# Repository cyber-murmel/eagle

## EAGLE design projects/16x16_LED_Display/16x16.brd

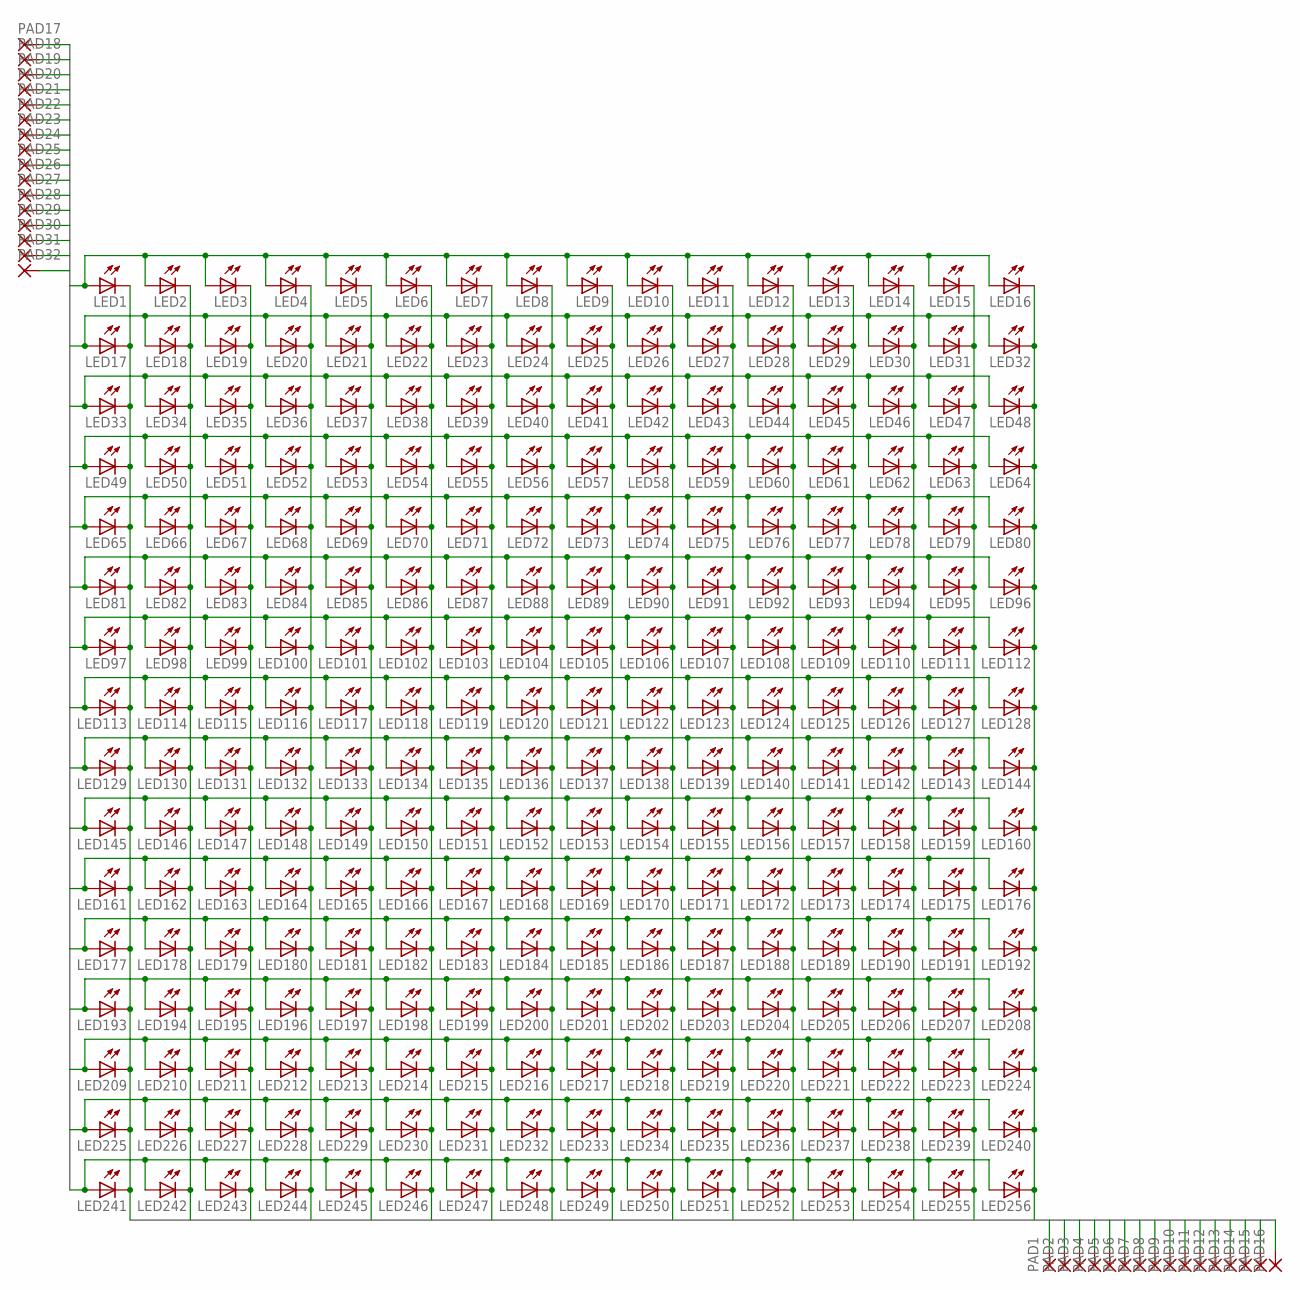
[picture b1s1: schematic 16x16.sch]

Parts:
LED1, LED2, LED3, LED4, LED5, LED6, LED7, LED8, LED9, LED10, LED11, LED12, LED13, LED14, LED15, LED16, LED17, LED18, LED19, LED20, LED21, LED22, LED23, LED24, LED25, LED26, LED27, LED28, LED29, LED30, LED31, LED32, LED33, LED34, LED35, LED36, LED37, LED38, LED39, LED40, LED41, LED42, LED43, LED44, LED45, LED46, LED47, LED48, LED49, LED50, LED51, LED52, LED53, LED54, LED55, LED56, LED57, LED58, LED59, LED60, LED61, LED62, LED63, LED64, LED65, LED66, LED67, LED68, LED69, LED70, LED71, LED72, LED73, LED74, LED75, LED76, LED77, LED78, LED79, LED80, LED81, LED82, LED83, LED84, LED85, LED86, LED87, LED88, LED89, LED90, LED91, LED92, LED93, LED94, LED95, LED96, LED97, LED98, LED99, LED100, LED101, LED102, LED103, LED104, LED105, LED106, LED107, LED108, LED109, LED110, LED111, LED112, LED113, LED114, LED115, LED116, LED117, LED118, LED119, LED120, LED121, LED122, LED123, LED124, LED125, LED126, LED127, LED128, LED129, LED130, LED131, LED132, LED133, LED134, LED135, LED136, LED137, LED138, LED139, LED140, LED141, LED142, LED143, LED144, LED145, LED146, LED147, LED148, LED149, LED150, LED151, LED152, LED153, LED154, LED155, LED156, LED157, LED158, LED159, LED160, LED161, LED162, LED163, LED164, LED165, LED166, LED167, LED168, LED169, LED170, LED171, LED172, LED173, LED174, LED175, LED176, LED177, LED178, LED179, LED180, LED181, LED182, LED183, LED184, LED185, LED186, LED187, LED188, LED189, LED190, LED191, LED192, LED193, LED194, LED195, LED196, LED197, LED198, LED199, LED200, LED201, LED202, LED203, LED204, LED205, LED206, LED207, LED208, LED209, LED210, LED211, LED212, LED213, LED214, LED215, LED216, LED217, LED218, LED219, LED220, LED221, LED222, LED223, LED224, LED225, LED226, LED227, LED228, LED229, LED230, LED231, LED232, LED233, LED234, LED235, LED236, LED237, LED238, LED239, LED240, LED241, LED242, LED243, LED244, LED245, LED246, LED247, LED248, LED249, LED250, LED251, LED252, LED253, LED254, LED255, LED256: LEDSML0603; SML0603
PAD1, PAD2, PAD3, PAD4, PAD5, PAD6, PAD7, PAD8, PAD9, PAD10, PAD11, PAD12, PAD13, PAD14, PAD15, PAD16, PAD17, PAD18, PAD19, PAD20, PAD21, PAD22, PAD23, PAD24, PAD25, PAD26, PAD27, PAD28, PAD29, PAD30, PAD31, PAD32: SMD2; SMD1,27-2,54

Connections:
X0: LED1.C, LED17.C, LED33.C, LED49.C, LED65.C, LED81.C, LED97.C, LED113.C, LED129.C, LED145.C, LED161.C, LED177.C, LED193.C, LED209.C, LED225.C, LED241.C, PAD1.1
X1: LED2.C, LED18.C, LED34.C, LED50.C, LED66.C, LED82.C, LED98.C, LED114.C, LED130.C, LED146.C, LED162.C, LED178.C, LED194.C, LED210.C, LED226.C, LED242.C, PAD2.1
X2: LED3.C, LED19.C, LED35.C, LED51.C, LED67.C, LED83.C, LED99.C, LED115.C, LED131.C, LED147.C, LED163.C, LED179.C, LED195.C, LED211.C, LED227.C, LED243.C, PAD3.1
X3: LED4.C, LED20.C, LED36.C, LED52.C, LED68.C, LED84.C, LED100.C, LED116.C, LED132.C, LED148.C, LED164.C, LED180.C, LED196.C, LED212.C, LED228.C, LED244.C, PAD4.1
X4: LED5.C, LED21.C, LED37.C, LED53.C, LED69.C, LED85.C, LED101.C, LED117.C, LED133.C, LED149.C, LED165.C, LED181.C, LED197.C, LED213.C, LED229.C, LED245.C, PAD5.1
X5: LED6.C, LED22.C, LED38.C, LED54.C, LED70.C, LED86.C, LED102.C, LED118.C, LED134.C, LED150.C, LED166.C, LED182.C, LED198.C, LED214.C, LED230.C, LED246.C, PAD6.1
X6: LED7.C, LED23.C, LED39.C, LED55.C, LED71.C, LED87.C, LED103.C, LED119.C, LED135.C, LED151.C, LED167.C, LED183.C, LED199.C, LED215.C, LED231.C, LED247.C, PAD7.1
X7: LED8.C, LED24.C, LED40.C, LED56.C, LED72.C, LED88.C, LED104.C, LED120.C, LED136.C, LED152.C, LED168.C, LED184.C, LED200.C, LED216.C, LED232.C, LED248.C, PAD8.1
X8: LED9.C, LED25.C, LED41.C, LED57.C, LED73.C, LED89.C, LED105.C, LED121.C, LED137.C, LED153.C, LED169.C, LED185.C, LED201.C, LED217.C, LED233.C, LED249.C, PAD9.1
X9: LED10.C, LED26.C, LED42.C, LED58.C, LED74.C, LED90.C, LED106.C, LED122.C, LED138.C, LED154.C, LED170.C, LED186.C, LED202.C, LED218.C, LED234.C, LED250.C, PAD10.1
X10: LED11.C, LED27.C, LED43.C, LED59.C, LED75.C, LED91.C, LED107.C, LED123.C, LED139.C, LED155.C, LED171.C, LED187.C, LED203.C, LED219.C, LED235.C, LED251.C, PAD11.1
X11: LED12.C, LED28.C, LED44.C, LED60.C, LED76.C, LED92.C, LED108.C, LED124.C, LED140.C, LED156.C, LED172.C, LED188.C, LED204.C, LED220.C, LED236.C, LED252.C, PAD12.1
X12: LED13.C, LED29.C, LED45.C, LED61.C, LED77.C, LED93.C, LED109.C, LED125.C, LED141.C, LED157.C, LED173.C, LED189.C, LED205.C, LED221.C, LED237.C, LED253.C, PAD13.1
X13: LED14.C, LED30.C, LED46.C, LED62.C, LED78.C, LED94.C, LED110.C, LED126.C, LED142.C, LED158.C, LED174.C, LED190.C, LED206.C, LED222.C, LED238.C, LED254.C, PAD14.1
X14: LED15.C, LED31.C, LED47.C, LED63.C, LED79.C, LED95.C, LED111.C, LED127.C, LED143.C, LED159.C, LED175.C, LED191.C, LED207.C, LED223.C, LED239.C, LED255.C, PAD15.1
X15: LED16.C, LED32.C, LED48.C, LED64.C, LED80.C, LED96.C, LED112.C, LED128.C, LED144.C, LED160.C, LED176.C, LED192.C, LED208.C, LED224.C, LED240.C, LED256.C, PAD16.1
Y0: LED1.A, LED2.A, LED3.A, LED4.A, LED5.A, LED6.A, LED7.A, LED8.A, LED9.A, LED10.A, LED11.A, LED12.A, LED13.A, LED14.A, LED15.A, LED16.A, PAD17.1
Y1: LED17.A, LED18.A, LED19.A, LED20.A, LED21.A, LED22.A, LED23.A, LED24.A, LED25.A, LED26.A, LED27.A, LED28.A, LED29.A, LED30.A, LED31.A, LED32.A, PAD18.1
Y2: LED33.A, LED34.A, LED35.A, LED36.A, LED37.A, LED38.A, LED39.A, LED40.A, LED41.A, LED42.A, LED43.A, LED44.A, LED45.A, LED46.A, LED47.A, LED48.A, PAD19.1
Y3: LED49.A, LED50.A, LED51.A, LED52.A, LED53.A, LED54.A, LED55.A, LED56.A, LED57.A, LED58.A, LED59.A, LED60.A, LED61.A, LED62.A, LED63.A, LED64.A, PAD20.1
Y4: LED65.A, LED66.A, LED67.A, LED68.A, LED69.A, LED70.A, LED71.A, LED72.A, LED73.A, LED74.A, LED75.A, LED76.A, LED77.A, LED78.A, LED79.A, LED80.A, PAD21.1
Y5: LED81.A, LED82.A, LED83.A, LED84.A, LED85.A, LED86.A, LED87.A, LED88.A, LED89.A, LED90.A, LED91.A, LED92.A, LED93.A, LED94.A, LED95.A, LED96.A, PAD22.1
Y6: LED97.A, LED98.A, LED99.A, LED100.A, LED101.A, LED102.A, LED103.A, LED104.A, LED105.A, LED106.A, LED107.A, LED108.A, LED109.A, LED110.A, LED111.A, LED112.A, PAD23.1
Y7: LED113.A, LED114.A, LED115.A, LED116.A, LED117.A, LED118.A, LED119.A, LED120.A, LED121.A, LED122.A, LED123.A, LED124.A, LED125.A, LED126.A, LED127.A, LED128.A, PAD24.1
Y8: LED129.A, LED130.A, LED131.A, LED132.A, LED133.A, LED134.A, LED135.A, LED136.A, LED137.A, LED138.A, LED139.A, LED140.A, LED141.A, LED142.A, LED143.A, LED144.A, PAD25.1
Y9: LED145.A, LED146.A, LED147.A, LED148.A, LED149.A, LED150.A, LED151.A, LED152.A, LED153.A, LED154.A, LED155.A, LED156.A, LED157.A, LED158.A, LED159.A, LED160.A, PAD26.1
Y10: LED161.A, LED162.A, LED163.A, LED164.A, LED165.A, LED166.A, LED167.A, LED168.A, LED169.A, LED170.A, LED171.A, LED172.A, LED173.A, LED174.A, LED175.A, LED176.A, PAD27.1
Y11: LED177.A, LED178.A, LED179.A, LED180.A, LED181.A, LED182.A, LED183.A, LED184.A, LED185.A, LED186.A, LED187.A, LED188.A, LED189.A, LED190.A, LED191.A, LED192.A, PAD28.1
Y12: LED193.A, LED194.A, LED195.A, LED196.A, LED197.A, LED198.A, LED199.A, LED200.A, LED201.A, LED202.A, LED203.A, LED204.A, LED205.A, LED206.A, LED207.A, LED208.A, PAD29.1
Y13: LED209.A, LED210.A, LED211.A, LED212.A, LED213.A, LED214.A, LED215.A, LED216.A, LED217.A, LED218.A, LED219.A, LED220.A, LED221.A, LED222.A, LED223.A, LED224.A, PAD30.1
Y14: LED225.A, LED226.A, LED227.A, LED228.A, LED229.A, LED230.A, LED231.A, LED232.A, LED233.A, LED234.A, LED235.A, LED236.A, LED237.A, LED238.A, LED239.A, LED240.A, PAD31.1
Y15: LED241.A, LED242.A, LED243.A, LED244.A, LED245.A, LED246.A, LED247.A, LED248.A, LED249.A, LED250.A, LED251.A, LED252.A, LED253.A, LED254.A, LED255.A, LED256.A, PAD32.1

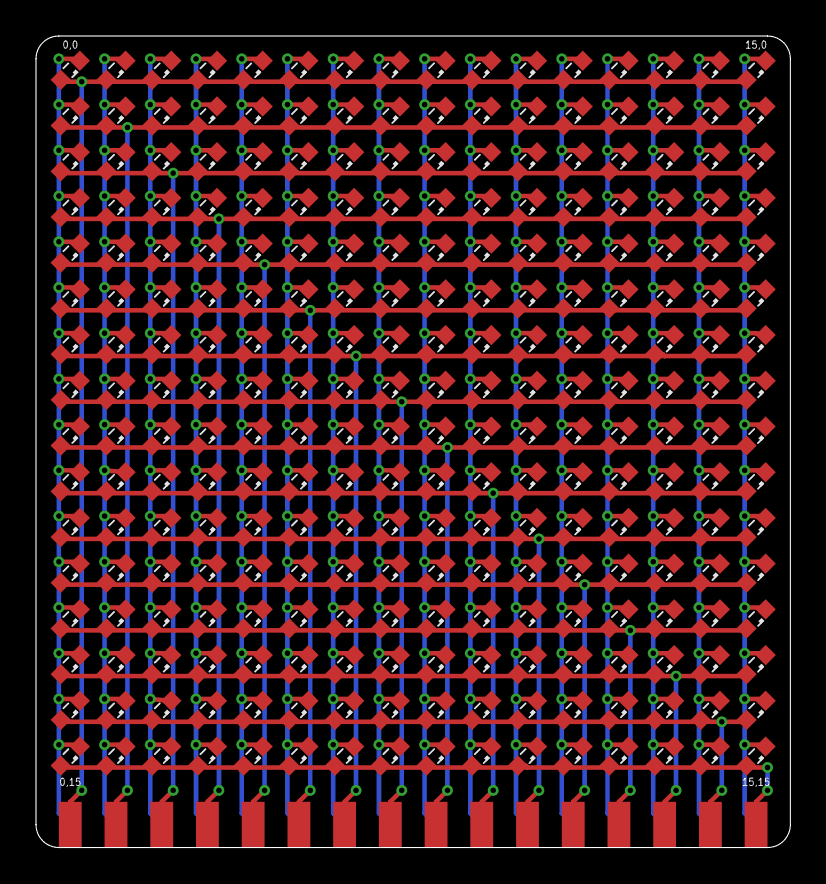
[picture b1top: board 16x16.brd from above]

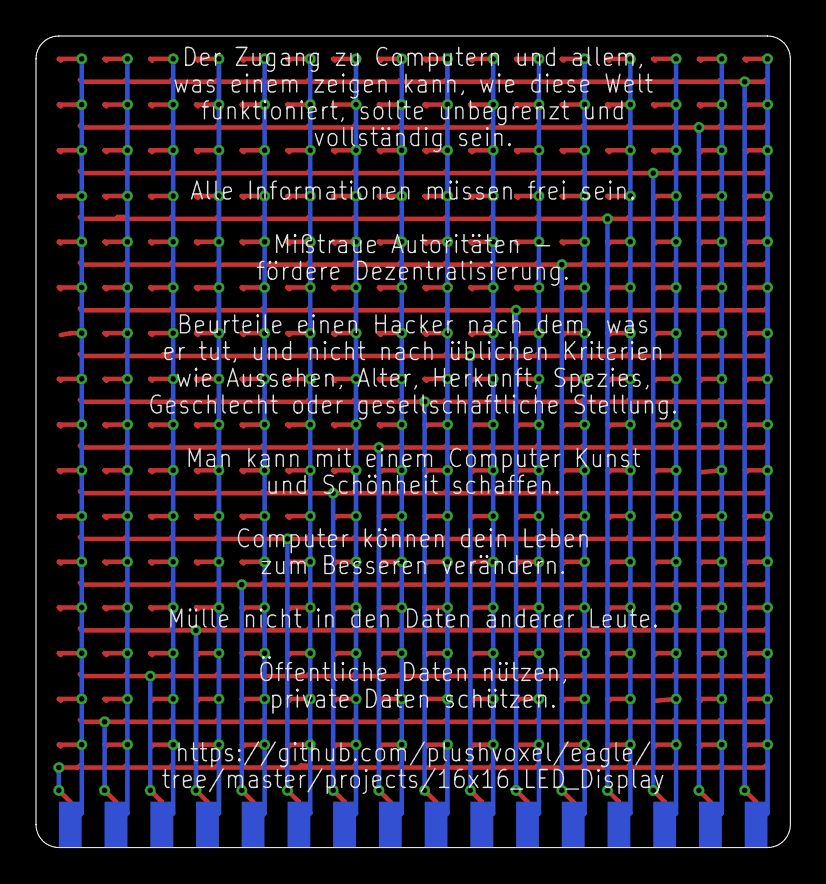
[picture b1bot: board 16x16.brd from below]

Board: 2 copper layers, 41.9 x 45.1 mm, 288 parts (16 on the bottom side), 32 nets.

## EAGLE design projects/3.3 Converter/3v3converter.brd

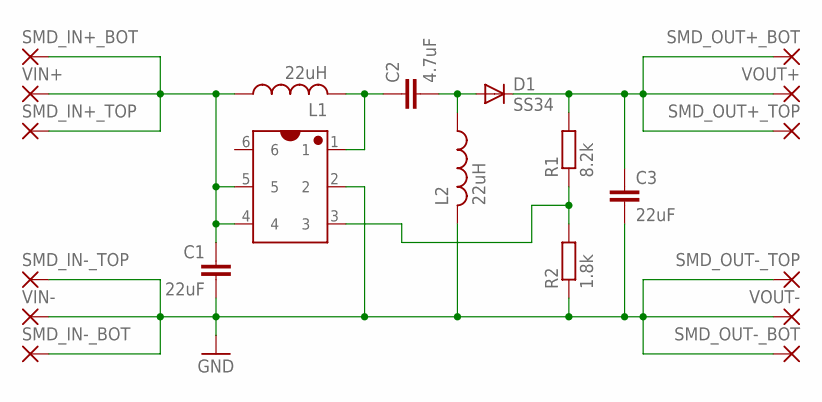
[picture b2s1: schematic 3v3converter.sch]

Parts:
C1, C3: 22uF; C0805
C2: 4.7uF; C0603
D1: SS34; DO214BA
L1, L2: 22uH; FPS
MT3608: mt3608; SOT-23-6
R1: 8.2k; R0603
R2: 1.8k; R0603
SMD_IN+_BOT: SMD5; SMD2,54-5,08
SMD_IN+_TOP: SMD5; SMD2,54-5,08
SMD_IN-_BOT: SMD5; SMD2,54-5,08
SMD_IN-_TOP: SMD5; SMD2,54-5,08
SMD_OUT+_BOT: SMD5; SMD2,54-5,08
SMD_OUT+_TOP: SMD5; SMD2,54-5,08
SMD_OUT-_BOT: SMD5; SMD2,54-5,08
SMD_OUT-_TOP: SMD5; SMD2,54-5,08
VIN+: 1,6/0,9
VIN-: 1,6/0,9
VOUT+: 1,6/0,9
VOUT-: 1,6/0,9

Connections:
GND: C1.2, C3.2, L2.P$2 (2), MT3608.2, R2.1, SMD_IN-_BOT.1, SMD_IN-_TOP.1, SMD_OUT-_BOT.1, SMD_OUT-_TOP.1, VIN-.1, VOUT-.1
unnamed: C1.1, L1.P$1 (1), MT3608.4, MT3608.5, SMD_IN+_BOT.1, SMD_IN+_TOP.1, VIN+.1
unnamed: C2.1, L1.P$2 (2), MT3608.1
unnamed: C2.2, D1.A, L2.P$1 (1)
unnamed: C3.1, D1.C, R1.2, SMD_OUT+_BOT.1, SMD_OUT+_TOP.1, VOUT+.1
unnamed: MT3608.3, R1.1, R2.2

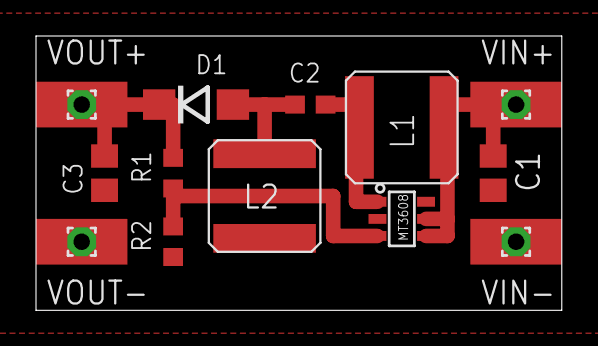
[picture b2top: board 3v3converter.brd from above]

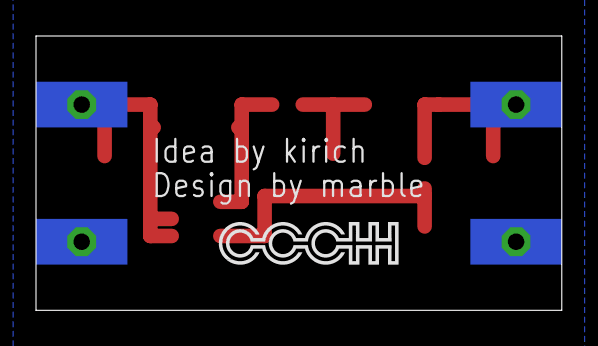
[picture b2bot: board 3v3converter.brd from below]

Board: 2 copper layers, 29.2 x 15.2 mm, 21 parts (4 on the bottom side), 6 nets.

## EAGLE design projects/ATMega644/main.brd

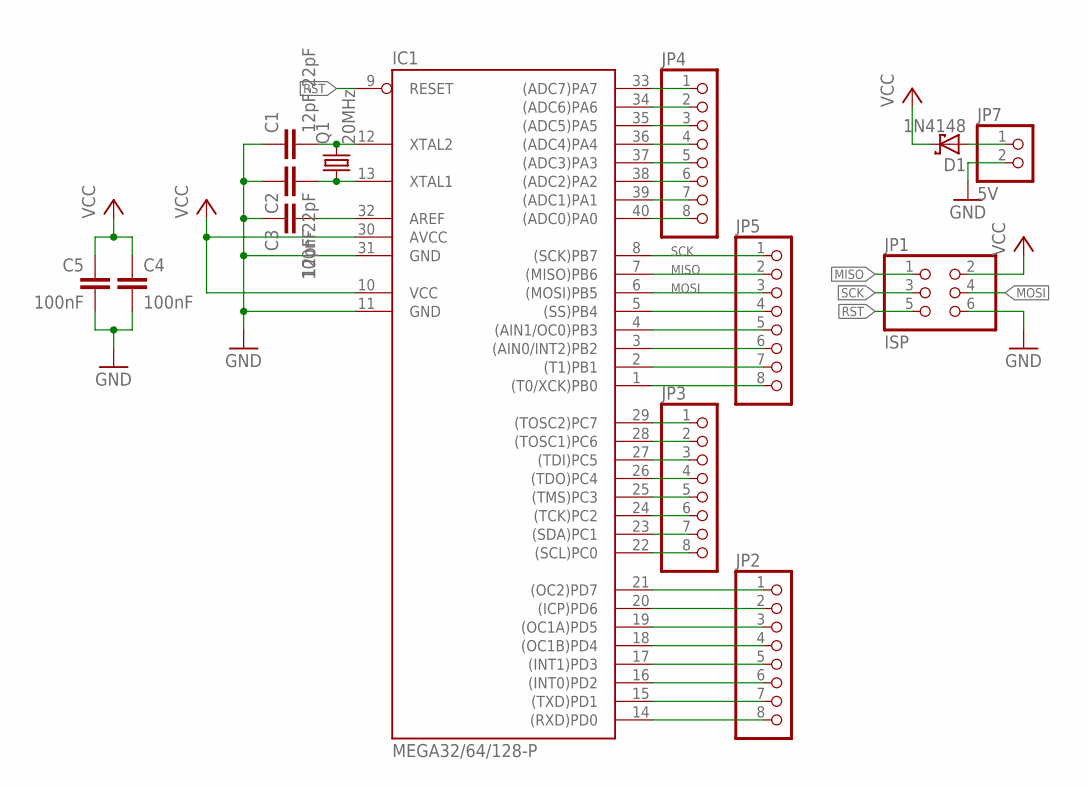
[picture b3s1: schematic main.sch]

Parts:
C1, C2: 12pF-22pF; C0805K
C3, C4, C5: 100nF; C0805K
D1: 1N4148; DO41-7.6
IC1: MEGA32/64/128-P; DIL40
JP1: ISP; 2X03
JP2, JP3, JP4, JP5: PINHD-1X8; 1X08
JP7: 5V; 1X02
Q1: 20MHz; CSM-7X-DU

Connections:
GND: C1.1, C2.1, C3.1, C4.2, C5.2, IC1.11 (GND), IC1.31 (GND), JP1.6, JP7.2
MISO: IC1.7 ((MISO)PB6), JP1.1, JP5.2
MOSI: IC1.6 ((MOSI)PB5), JP1.4, JP5.3
unnamed: C2.2, IC1.13 (XTAL1), Q1.1
unnamed: C1.2, IC1.12 (XTAL2), Q1.2
unnamed: D1.A, JP7.1
unnamed: C3.2, IC1.32 (AREF)
unnamed: IC1.5 ((SS)PB4), JP5.4
unnamed: IC1.4 ((AIN1/OC0)PB3), JP5.5
unnamed: IC1.21 ((OC2)PD7), JP2.1
unnamed: IC1.20 ((ICP)PD6), JP2.2
unnamed: IC1.19 ((OC1A)PD5), JP2.3
unnamed: IC1.18 ((OC1B)PD4), JP2.4
unnamed: IC1.17 ((INT1)PD3), JP2.5
unnamed: IC1.16 ((INT0)PD2), JP2.6
unnamed: IC1.15 ((TXD)PD1), JP2.7
unnamed: IC1.14 ((RXD)PD0), JP2.8
unnamed: IC1.29 ((TOSC2)PC7), JP3.1
unnamed: IC1.28 ((TOSC1)PC6), JP3.2
unnamed: IC1.27 ((TDI)PC5), JP3.3
unnamed: IC1.26 ((TDO)PC4), JP3.4
unnamed: IC1.25 ((TMS)PC3), JP3.5
unnamed: IC1.24 ((TCK)PC2), JP3.6
unnamed: IC1.23 ((SDA)PC1), JP3.7
unnamed: IC1.22 ((SCL)PC0), JP3.8
unnamed: IC1.33 ((ADC7)PA7), JP4.1
unnamed: IC1.34 ((ADC6)PA6), JP4.2
unnamed: IC1.35 ((ADC5)PA5), JP4.3
unnamed: IC1.36 ((ADC4)PA4), JP4.4
unnamed: IC1.37 ((ADC3)PA3), JP4.5
unnamed: IC1.38 ((ADC2)PA2), JP4.6
unnamed: IC1.39 ((ADC1)PA1), JP4.7
unnamed: IC1.40 ((ADC0)PA0), JP4.8
unnamed: IC1.3 ((AIN0/INT2)PB2), JP5.6
unnamed: IC1.2 ((T1)PB1), JP5.7
unnamed: IC1.1 ((T0/XCK)PB0), JP5.8
RST: IC1.9 (RESET), JP1.5
SCK: IC1.8 ((SCK)PB7), JP1.3, JP5.1
VCC: C4.1, C5.1, D1.C, IC1.10 (VCC), IC1.30 (AVCC), JP1.2

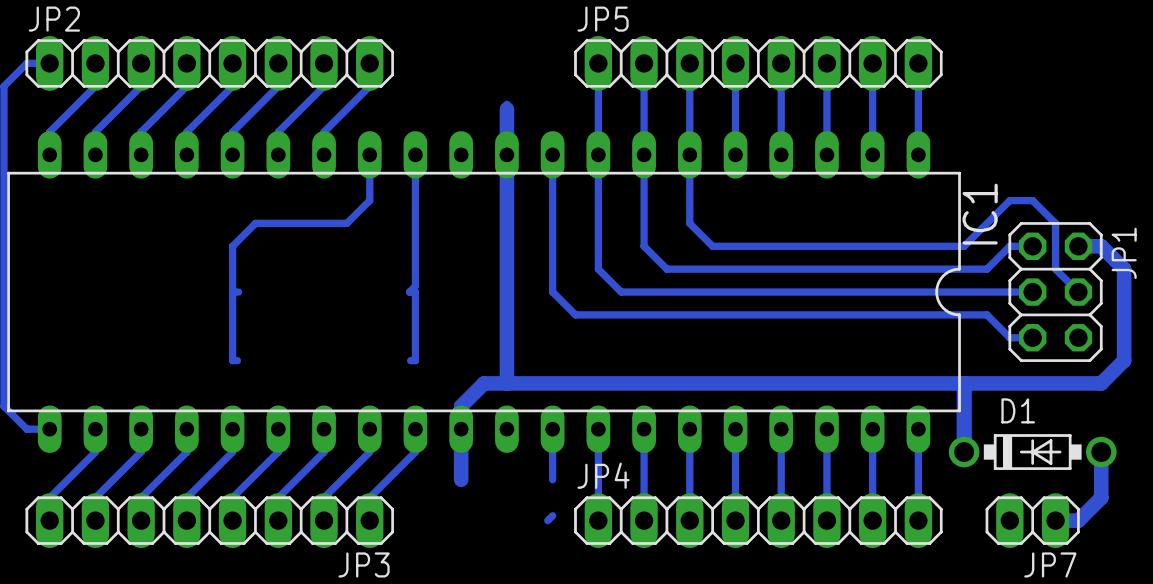
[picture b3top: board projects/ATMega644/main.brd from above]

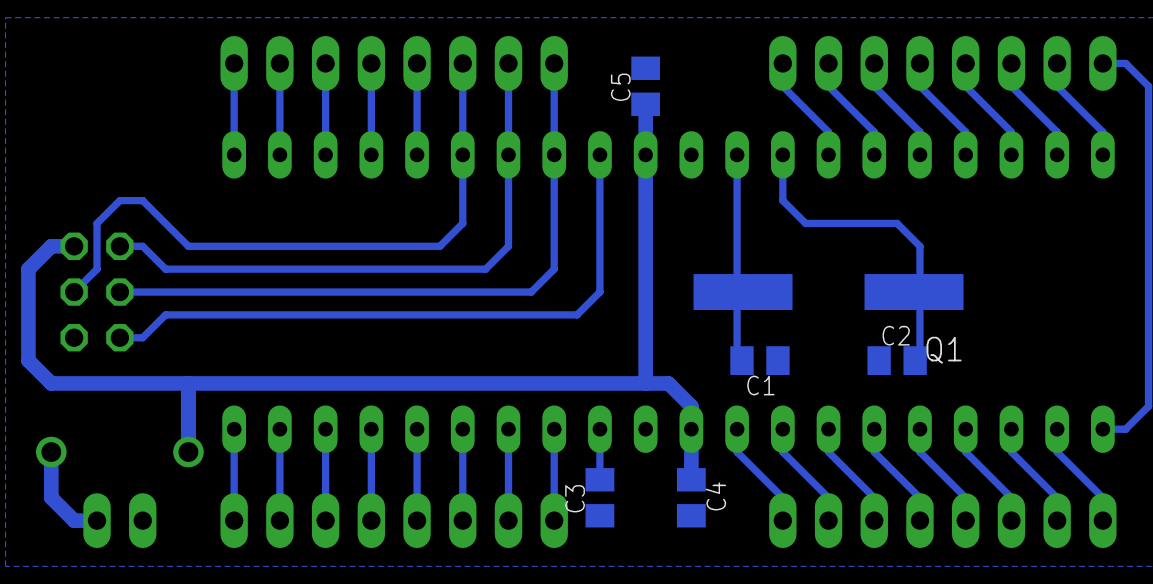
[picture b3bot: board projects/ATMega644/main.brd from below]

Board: 2 copper layers, 14 parts (6 on the bottom side), 39 nets.

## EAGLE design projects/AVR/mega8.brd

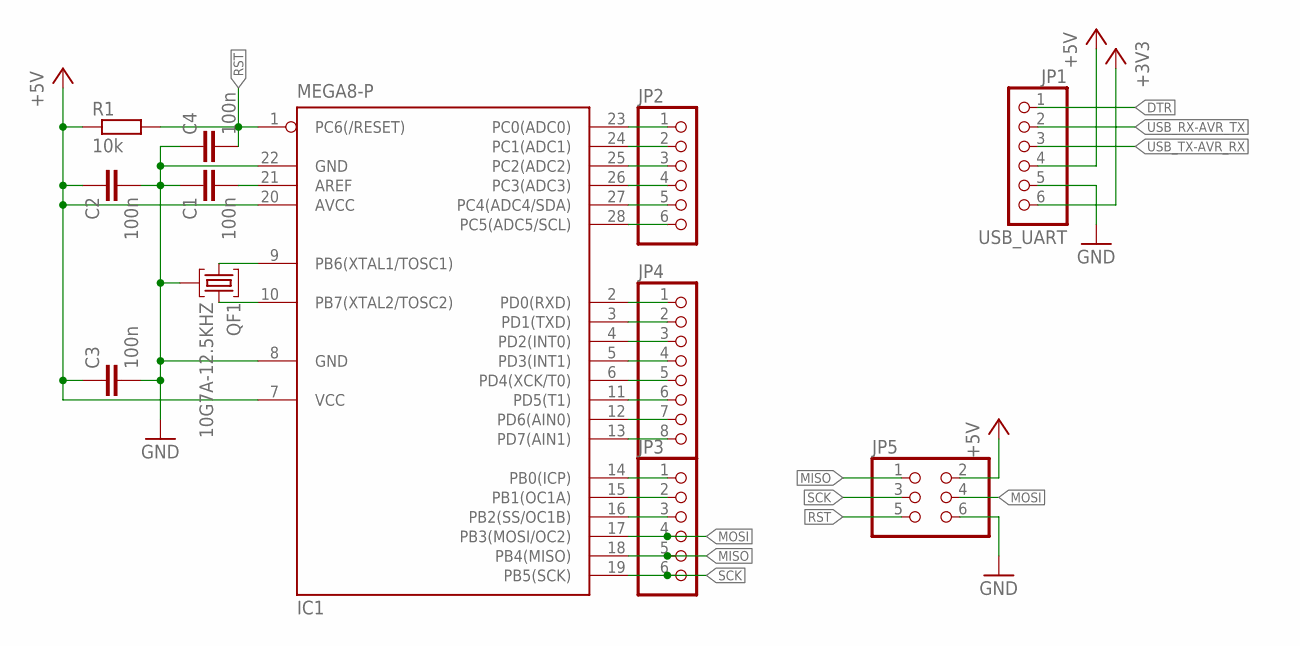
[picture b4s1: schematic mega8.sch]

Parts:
C1, C2, C3, C4: 100n; C0603
IC1: MEGA8-P; DIL28-3
JP1: USB_UART; 1X06
JP2, JP3: PINHD-1X6; 1X06
JP4: PINHD-1X8; 1X08
JP5: PINHD-2X3; 2X03
QF1: 10G7A-12.5KHZ; HC49U
R1: 10k; R0603

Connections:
+3V3: JP1.6
+5V: C2.1, C3.1, IC1.7 (VCC), IC1.20 (AVCC), JP1.4, JP5.2, R1.1
DTR: JP1.1
GND: C1.1, C2.2, C3.2, C4.1, IC1.8 (GND), IC1.22 (GND), JP1.5, JP5.6, QF1.2
MISO: IC1.18 (PB4(MISO)), JP3.5, JP5.1
MOSI: IC1.17 (PB3(MOSI/OC2)), JP3.4, JP5.4
unnamed: IC1.9 (PB6(XTAL1/TOSC1)), QF1.1
unnamed: IC1.10 (PB7(XTAL2/TOSC2)), QF1.3
unnamed: IC1.23 (PC0(ADC0)), JP2.1
unnamed: C1.2, IC1.21 (AREF)
unnamed: IC1.24 (PC1(ADC1)), JP2.2
unnamed: IC1.25 (PC2(ADC2)), JP2.3
unnamed: IC1.26 (PC3(ADC3)), JP2.4
unnamed: IC1.27 (PC4(ADC4/SDA)), JP2.5
unnamed: IC1.28 (PC5(ADC5/SCL)), JP2.6
unnamed: IC1.14 (PB0(ICP)), JP3.1
unnamed: IC1.15 (PB1(OC1A)), JP3.2
unnamed: IC1.16 (PB2(SS/OC1B)), JP3.3
unnamed: IC1.2 (PD0(RXD)), JP4.1
unnamed: IC1.3 (PD1(TXD)), JP4.2
unnamed: IC1.4 (PD2(INT0)), JP4.3
unnamed: IC1.5 (PD3(INT1)), JP4.4
unnamed: IC1.6 (PD4(XCK/T0)), JP4.5
unnamed: IC1.11 (PD5(T1)), JP4.6
unnamed: IC1.12 (PD6(AIN0)), JP4.7
unnamed: IC1.13 (PD7(AIN1)), JP4.8
RST: C4.2, IC1.1 (PC6(/RESET)), JP5.5, R1.2
SCK: IC1.19 (PB5(SCK)), JP3.6, JP5.3
USB_RX-AVR_TX: JP1.2
USB_TX-AVR_RX: JP1.3

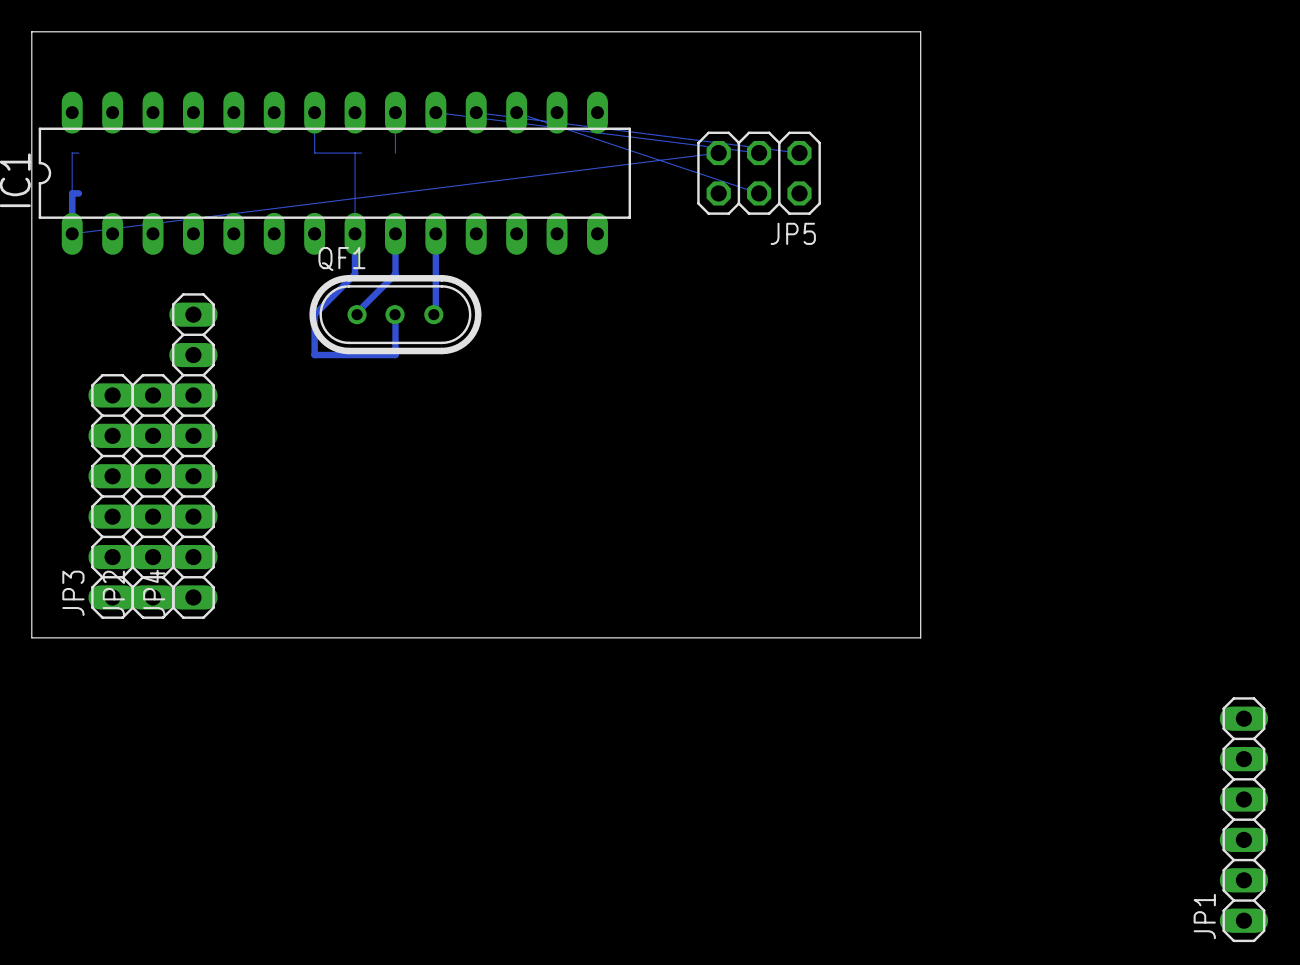
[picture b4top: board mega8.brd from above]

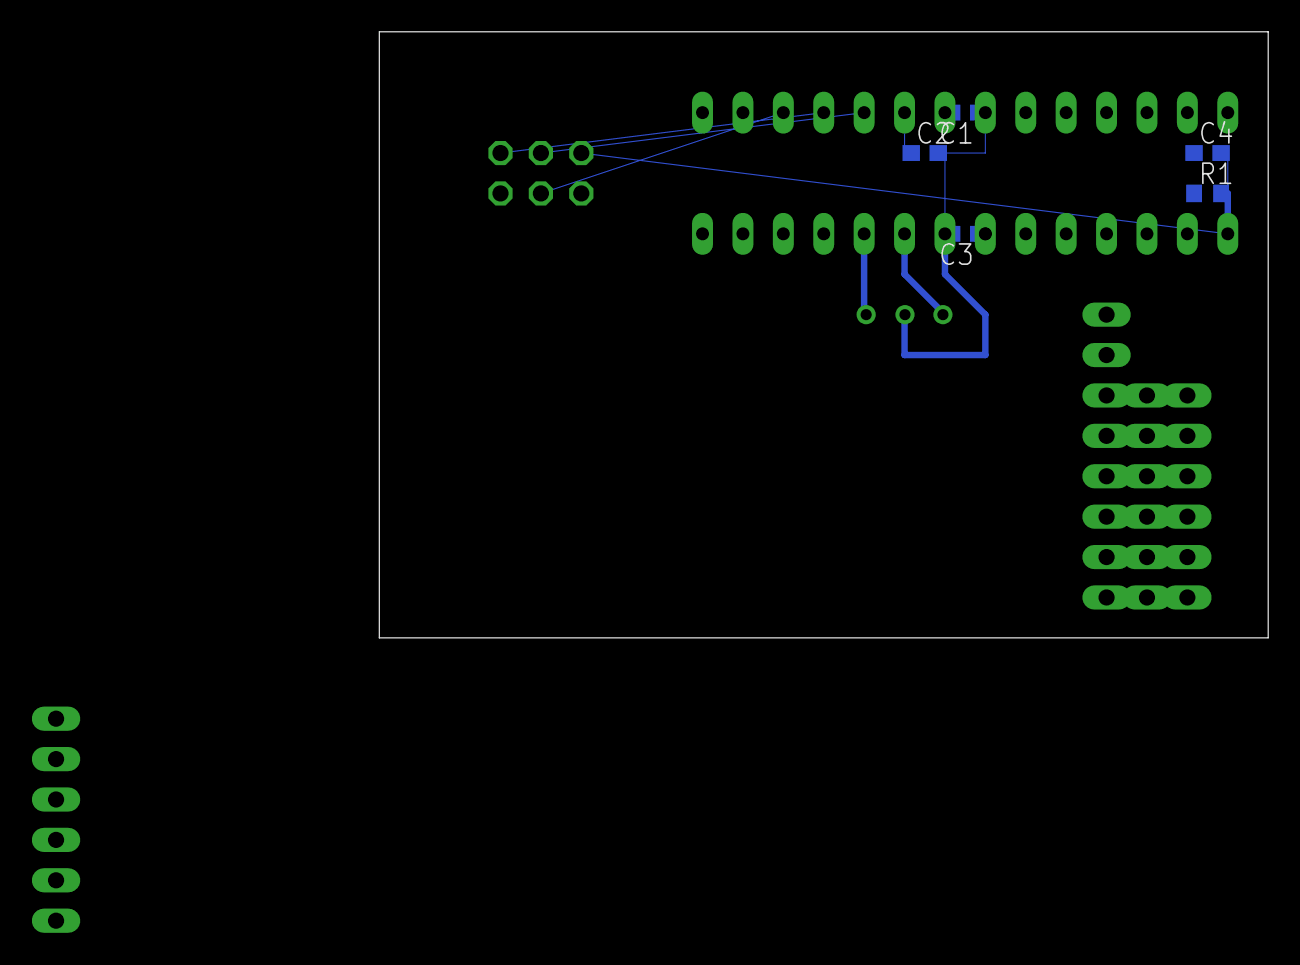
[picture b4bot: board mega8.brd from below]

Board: 2 copper layers, 55.9 x 38.1 mm, 12 parts (5 on the bottom side), 26 nets.

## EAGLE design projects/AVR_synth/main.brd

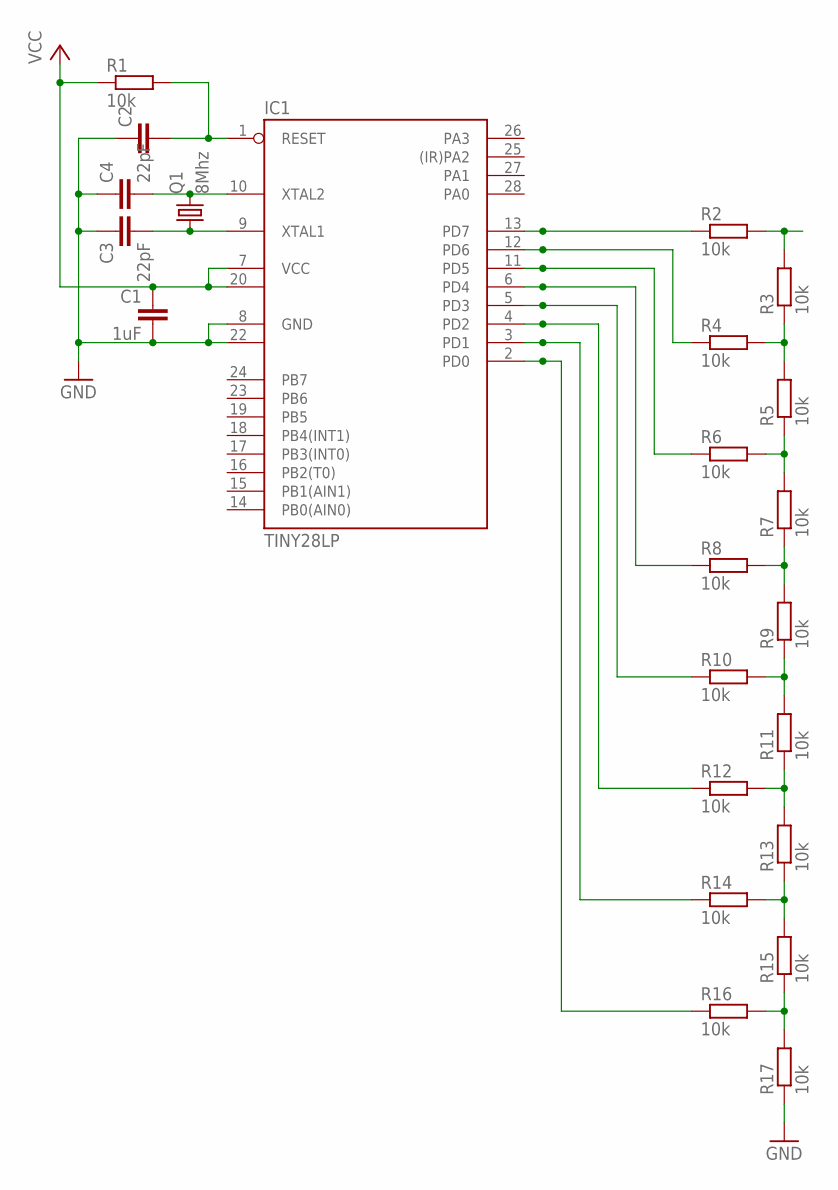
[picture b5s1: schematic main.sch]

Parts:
C1: 1uF; C1206
C2: C-EUC1206; C1206
C3, C4: 22pF; C1206
IC1: TINY28LP; DIL28-3
Q1: 8Mhz; HC49/S
R1, R2, R3, R4, R5, R6, R7, R8, R9, R10, R11, R12, R13, R14, R15, R16, R17: 10k; R1206

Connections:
GND: C1.2, C2.1, C3.1, C4.1, IC1.8 (GND), IC1.22 (GND1), R17.1
unnamed: C4.2, IC1.10 (XTAL2), Q1.2
unnamed: C3.2, IC1.9 (XTAL1), Q1.1
unnamed: R3.1, R4.2, R5.2
unnamed: R2.2, R3.2
unnamed: C2.2, IC1.1 (RESET), R1.2
unnamed: R5.1, R6.2, R7.2
unnamed: R7.1, R8.2, R9.2
unnamed: R11.1, R12.2, R13.2
unnamed: R9.1, R10.2, R11.2
unnamed: R13.1, R14.2, R15.2
unnamed: R15.1, R16.2, R17.2
unnamed: IC1.13 (PD7), R2.1
unnamed: IC1.12 (PD6), R4.1
unnamed: IC1.11 (PD5), R6.1
unnamed: IC1.6 (PD4), R8.1
unnamed: IC1.5 (PD3), R10.1
unnamed: IC1.4 (PD2), R12.1
unnamed: IC1.3 (PD1), R14.1
unnamed: IC1.2 (PD0), R16.1
VCC: C1.1, IC1.7 (VCC), IC1.20 (VCC1), R1.1

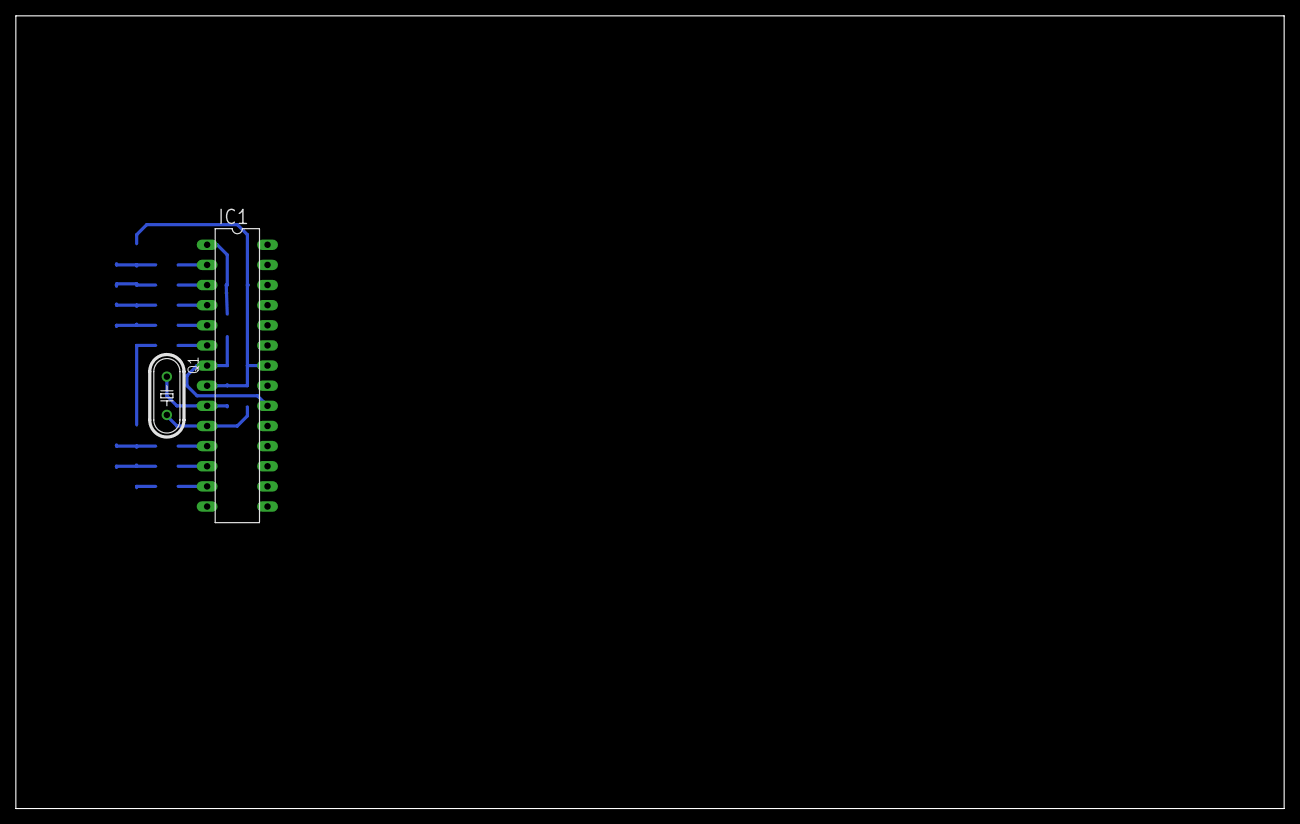
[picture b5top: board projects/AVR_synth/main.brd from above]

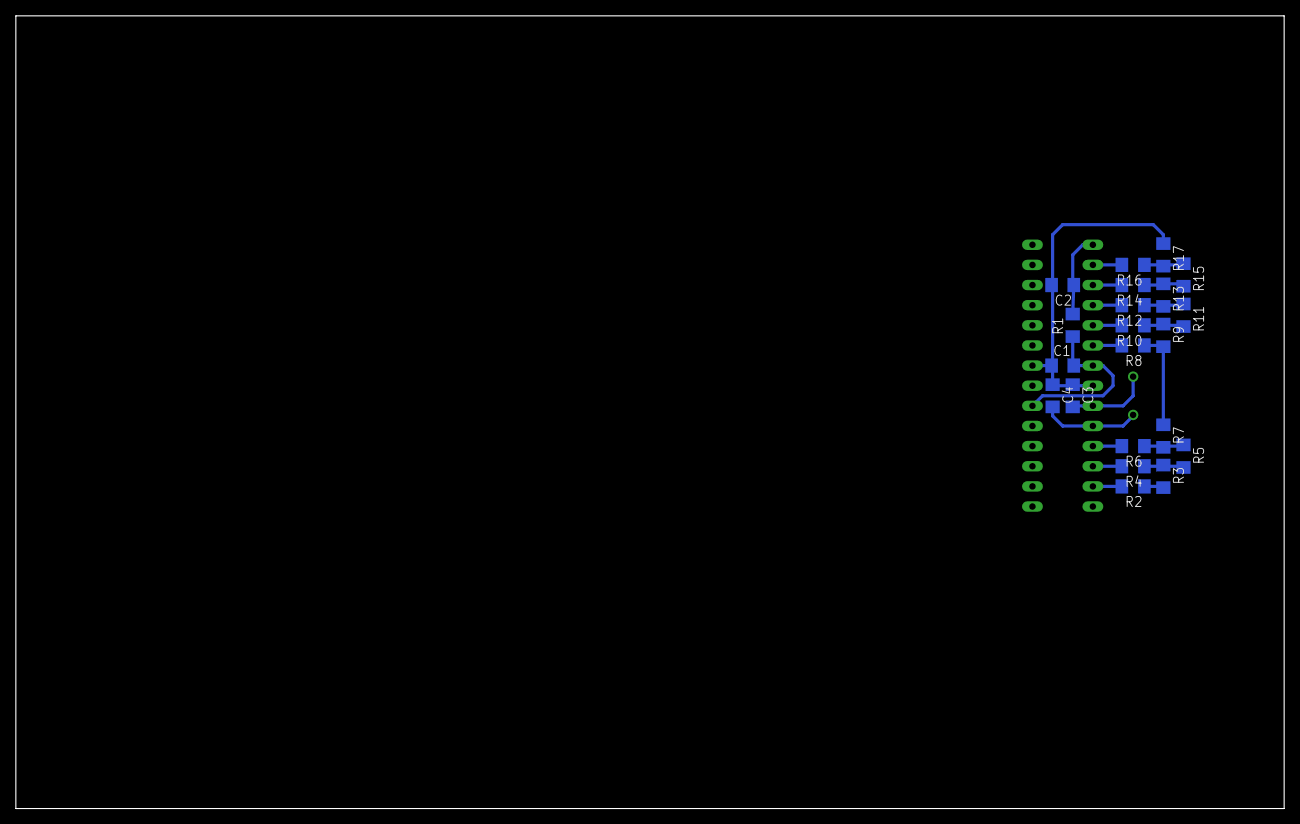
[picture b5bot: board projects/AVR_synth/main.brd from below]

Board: 2 copper layers, 160.0 x 100.0 mm, 23 parts (21 on the bottom side), 21 nets.

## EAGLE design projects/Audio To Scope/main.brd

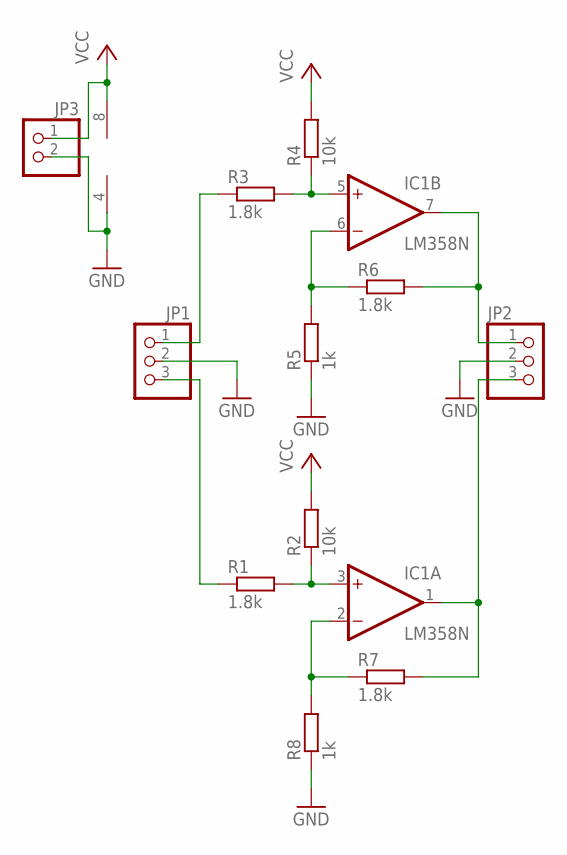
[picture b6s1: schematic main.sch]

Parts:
IC1: LM358N; DIL08
JP1, JP2: PINHD-1X3; 1X03
JP3: PINHD-1X2; 1X02
R1, R3, R6, R7: 1.8k; 0204/7
R2, R4: 10k; 0204/7
R5, R8: 1k; 0204/7

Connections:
GND: IC1.4 (V-), JP1.2, JP2.2, JP3.2, R5.1, R8.1
unnamed: IC1.5 (+IN), R3.2, R4.1
unnamed: IC1.3 (+IN), R1.2, R2.1
unnamed: IC1.6 (-IN), R5.2, R6.1
unnamed: IC1.7 (OUT), JP2.1, R6.2
unnamed: IC1.2 (-IN), R7.1, R8.2
unnamed: IC1.1 (OUT), JP2.3, R7.2
unnamed: JP1.1, R3.1
unnamed: JP1.3, R1.1
VCC: IC1.8 (V+), JP3.1, R2.2, R4.2

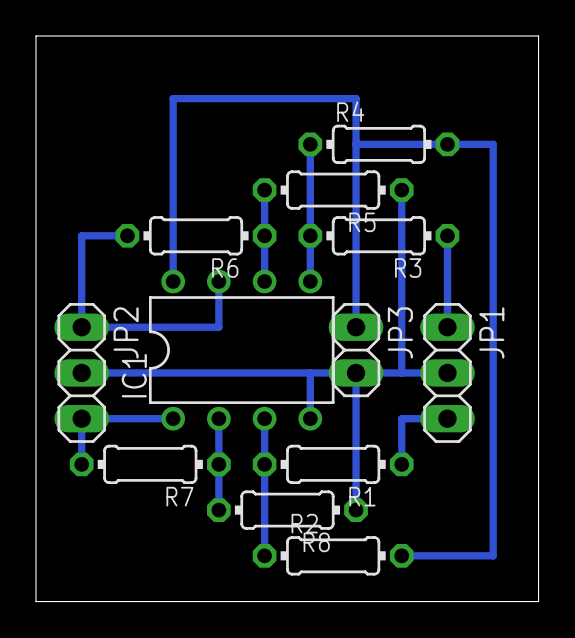
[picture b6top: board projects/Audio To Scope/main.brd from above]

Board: 2 copper layers, 27.9 x 31.4 mm, 12 parts (0 on the bottom side), 10 nets.

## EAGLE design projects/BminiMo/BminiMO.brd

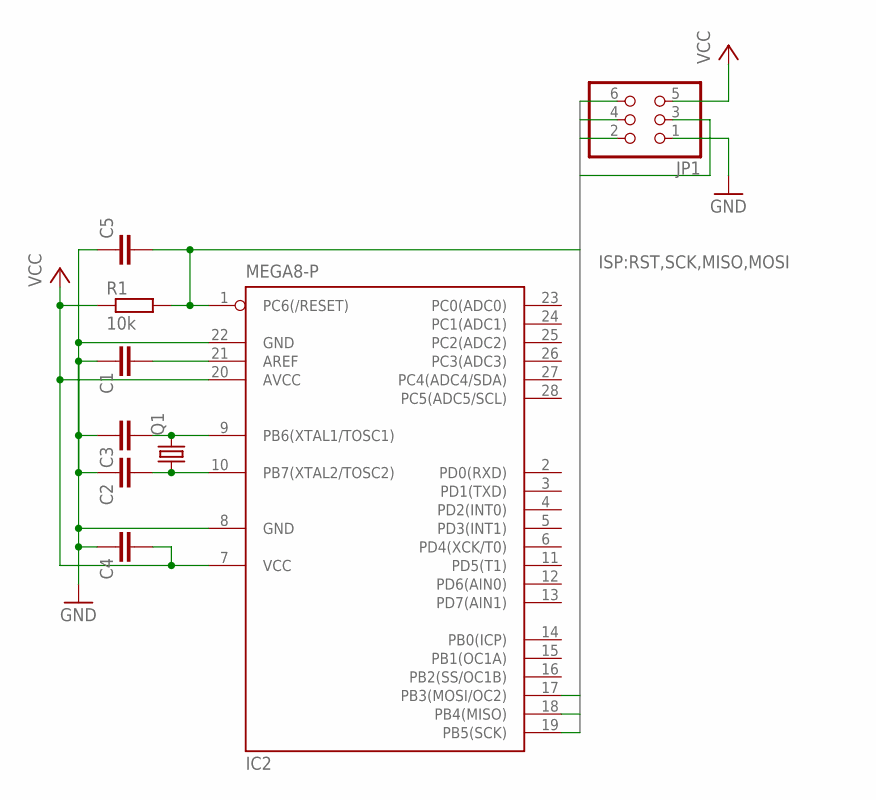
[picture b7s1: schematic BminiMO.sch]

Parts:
C1, C2, C3, C4, C5: C-EU025-025X050; C025-025X050
IC2: MEGA8-P; DIL28-3
JP1: PINHD-2X3/90; 2X03/90
Q1: CRYSTALHC49U-V; HC49U-V
R1: 10k; 0207/10

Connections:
GND: C1.1, C2.1, C3.1, C4.1, C5.1, IC2.8 (GND), IC2.22 (GND), JP1.1
MISO: IC2.18 (PB4(MISO)), JP1.6
MOSI: IC2.17 (PB3(MOSI/OC2)), JP1.3
unnamed: C3.2, IC2.9 (PB6(XTAL1/TOSC1)), Q1.2
unnamed: C2.2, IC2.10 (PB7(XTAL2/TOSC2)), Q1.1
unnamed: C1.2, IC2.21 (AREF)
RST: C5.2, IC2.1 (PC6(/RESET)), JP1.2, R1.2
SCK: IC2.19 (PB5(SCK)), JP1.4
VCC: C4.2, IC2.7 (VCC), IC2.20 (AVCC), JP1.5, R1.1
